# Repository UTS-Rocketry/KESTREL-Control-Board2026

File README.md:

# CAS Interface Board 2026

Control Actuation System (CAS) Interface Board for the UTS Rocketry avionics stack.

This board provides closed-loop control for the airbrake and parafoil control systems, along with sensor interfaces and onboard data logging. The design is based on the STM32F405RGT6 microcontroller and integrates inertial sensing, actuator control, and non-volatile storage.

The CAS board is intended to operate as part of the UTS Rocketry flight avionics architecture.

---

## Overview

The CAS Interface Board is responsible for:

- Airbrake deployment control
- Roll stabilisation control
- Sensor acquisition
- Data logging
- Actuator interfacing

Closed-loop control is performed onboard using IMU, barometric sensor, and GPS measurements.

---

## Hardware

### Microcontroller

STM32F405RGT6

- ARM Cortex-M4F
- 168 MHz
- Hardware floating point
- 1 MB Flash
- 192 KB RAM

---

### Sensors

#### IMU

LSM6DS3TR-C

Interface:

- SPI (4-wire)

Signals:

- SCK
- MOSI
- MISO
- CS
- DRDY Interrupt

Power:

- 3.3 V

---

#### Barometer

Interface:

- I2C

Signals:

- SCL
- SDA

Power:

- 3.3 V

---

### Storage

#### MicroSD Card

Interface:

- SPI

Signals:

- SCK
- MOSI
- MISO
- CS

Purpose:

- Flight data logging

---

### Actuator Interfaces

#### Servo Outputs

- Airbrake Servo
- Roll Control Servo

Control Method:

- Timer PWM outputs

Power:

- Dedicated 5 V servo rail

Signal Voltage:

- 3.3 V logic

---

## Control System

### Airbrake Control

The CAS system predicts apogee using altitude and velocity estimates derived from sensor measurements.

Airbrake deployment is adjusted to reach the target apogee.

Inputs:

- Barometer altitude
- Estimated vertical velocity

Outputs:

- Airbrake servo PWM

## Firmware

Development tools:

- STM32CubeMX
- STM32CubeIDE
- ST-Link

Features:

- SPI IMU driver
- I2C barometer driver
- PWM servo control
- SD card logging
- Flash logging
- Interrupt-driven sensor acquisition

---

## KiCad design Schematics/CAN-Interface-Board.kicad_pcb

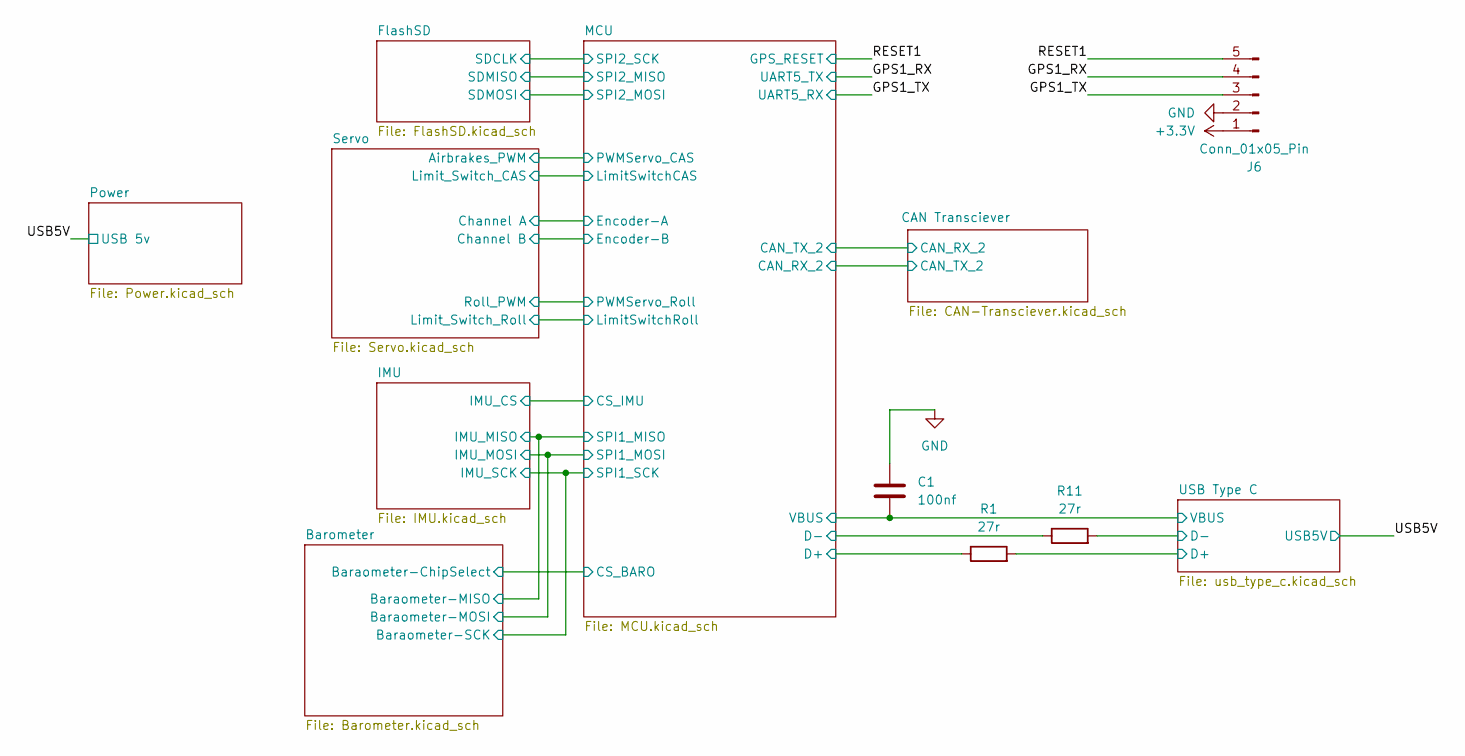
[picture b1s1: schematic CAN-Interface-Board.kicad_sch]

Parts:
C1: 100nf; C_0805_2012Metric_Pad1.18x1.45mm_HandSolder; LCSC C49678
J6: Conn_01x05_Pin; JST_XH_B5B-XH-A_1x05_P2.50mm_Vertical; LCSC C157991
R1, R11: 27r; R_0805_2012Metric_Pad1.20x1.40mm_HandSolder; LCSC C17594

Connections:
+3.3V: J6.1; also elsewhere on the board
/GPS1_RX: J6.4; also elsewhere on the board
/GPS1_TX: J6.3; also elsewhere on the board
/MCU/D+: R1.1; also elsewhere on the board
/MCU/D-: R11.1; also elsewhere on the board
/RESET1: J6.5; also elsewhere on the board
/USB5V: C1.2; also elsewhere on the board
/USB Type C/D+: R1.2; also elsewhere on the board
/USB Type C/D-: R11.2; also elsewhere on the board
GND: C1.1, J6.2; also elsewhere on the board

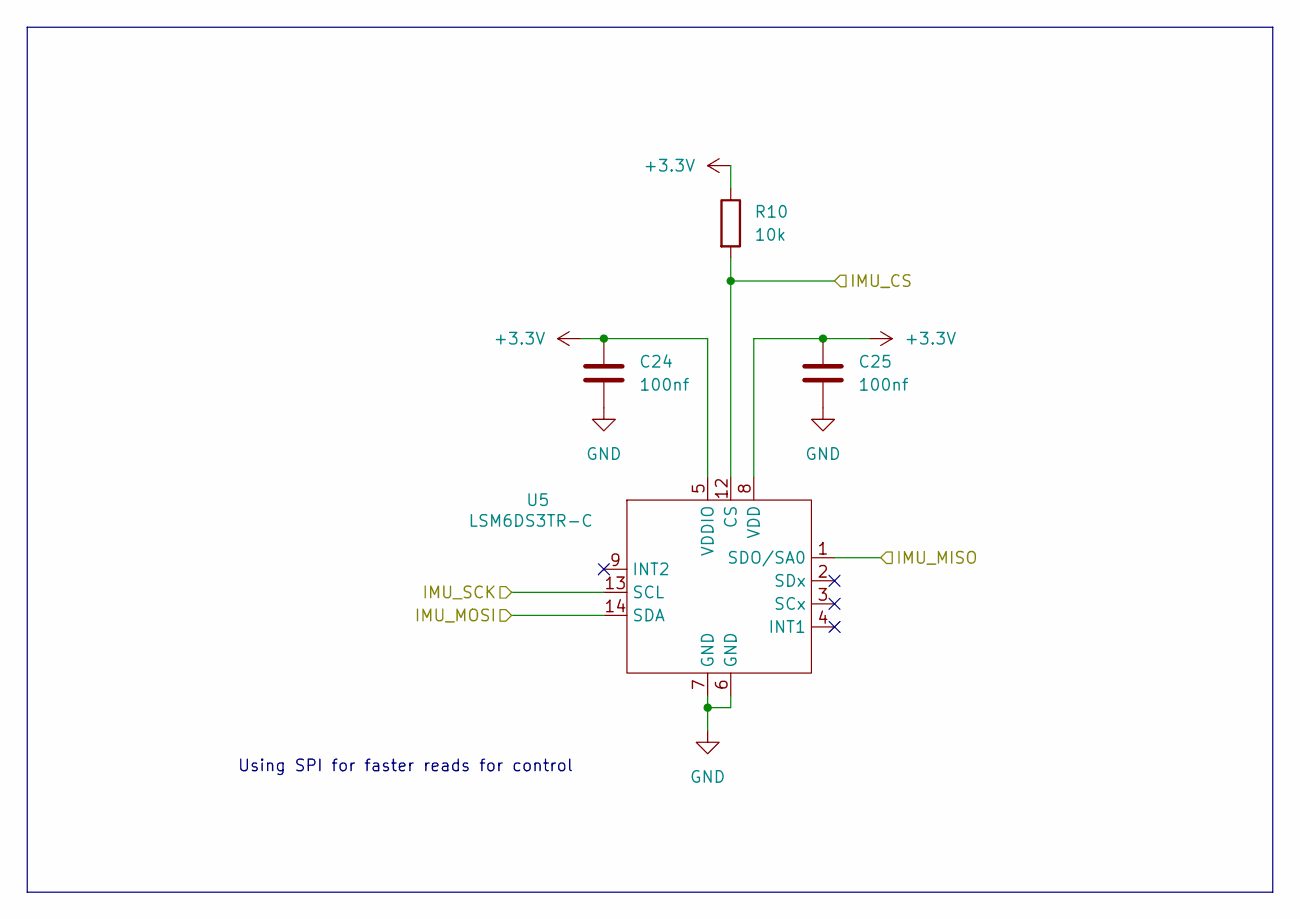
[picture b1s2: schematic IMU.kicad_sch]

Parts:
C24, C25: 100nf; C_0805_2012Metric_Pad1.18x1.45mm_HandSolder; LCSC Part C49678
R10: 10k; R_0805_2012Metric_Pad1.20x1.40mm_HandSolder; LCSC C84376
U5: LSM6DS3TR-C; LGA-14-2.5X3MM; LCSC Part C967633

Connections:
+3.3V: C24.1, C25.1, R10.1, U5.5 (VDDIO), U5.8 (VDD); also elsewhere on the board
/Barometer/Baraometer-MISO: U5.1 (SDO/SA0); also elsewhere on the board
/Barometer/Baraometer-MOSI: U5.14 (SDA); also elsewhere on the board
/Barometer/Baraometer-SCK: U5.13 (SCL); also elsewhere on the board
/IMU/IMU_CS: R10.2, U5.12 (CS); also elsewhere on the board
GND: C24.2, C25.2, U5.6 (GND), U5.7 (GND); also elsewhere on the board

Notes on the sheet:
Using SPI for faster reads for control

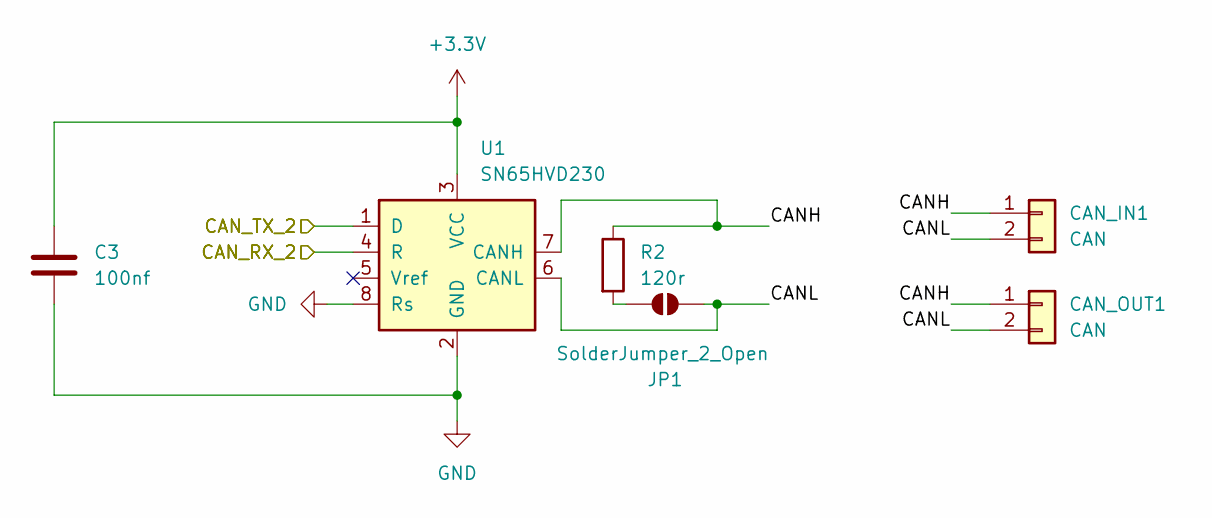
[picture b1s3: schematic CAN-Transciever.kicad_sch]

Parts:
C3: 100nf; C_0805_2012Metric_Pad1.18x1.45mm_HandSolder; LCSC Part C49678
CAN_IN1: CAN; MOLEX_26013114; LCSC Part C17644051
CAN_OUT1: CAN; MOLEX_26013114; LCSC Part C17644051
JP1: SolderJumper_2_Open; SolderJumper-2_P1.3mm_Open_TrianglePad1.0x1.5mm; LCSC C474893
R2: 120r; R_0805_2012Metric_Pad1.20x1.40mm_HandSolder; LCSC Part C269726
U1: SN65HVD230; SOIC-8_3.9x4.9mm_P1.27mm; LCSC Part C1543812

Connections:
+3.3V: C3.1, U1.3 (VCC); also elsewhere on the board
/CAN Transciever/CANH: CAN_IN1.1, CAN_OUT1.1, R2.1, U1.7 (CANH)
/CAN Transciever/CANL: CAN_IN1.2, CAN_OUT1.2, JP1.2 (B), U1.6 (CANL)
/CAN Transciever/CAN_RX_2: U1.4 (R); also elsewhere on the board
/CAN Transciever/CAN_TX_2: U1.1 (D); also elsewhere on the board
GND: C3.2, U1.2 (GND), U1.8 (Rs); also elsewhere on the board
unnamed: JP1.1 (A), R2.2

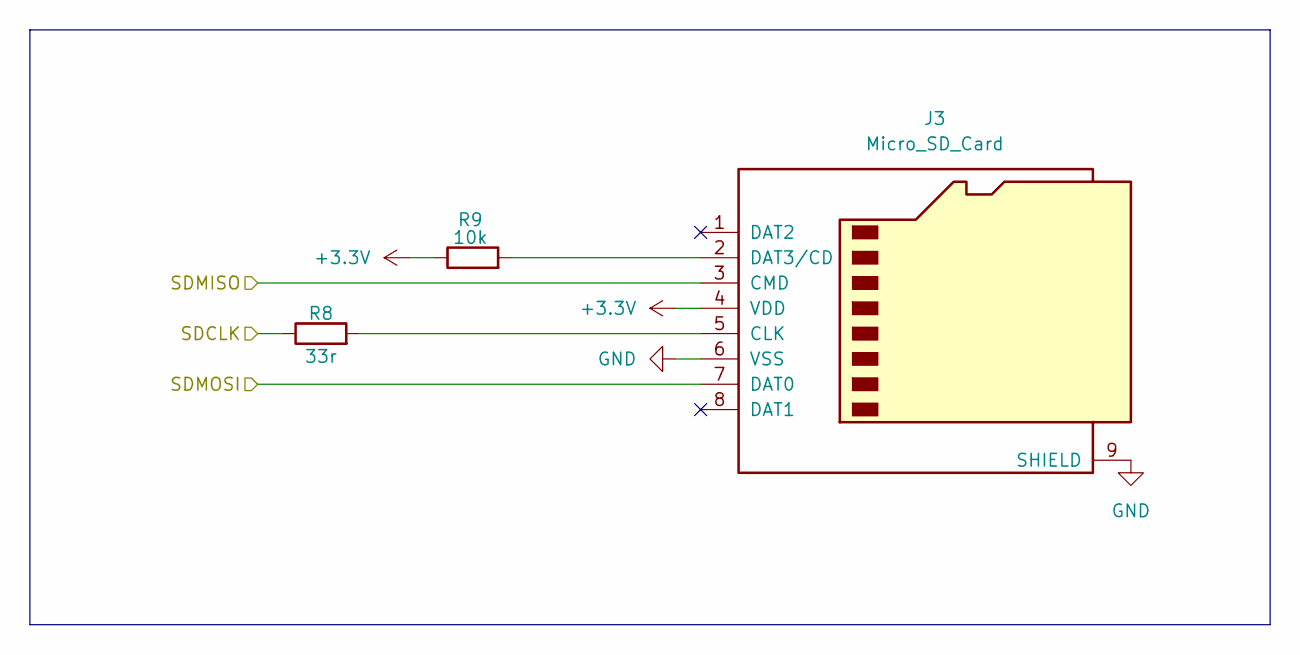
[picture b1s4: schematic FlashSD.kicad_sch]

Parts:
J3: Micro_SD_Card; microSD_HC_Molex_47219-2001; LCSC Part C164170
R8: 33r; R_0805_2012Metric_Pad1.20x1.40mm_HandSolder; LCSC Part C17557
R9: 10k; R_0805_2012Metric_Pad1.20x1.40mm_HandSolder; LCSC Part C84376

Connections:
+3.3V: J3.4 (VDD), R9.1; also elsewhere on the board
/FlashSD/SDCLK: R8.1; also elsewhere on the board
/FlashSD/SDMISO: J3.3 (CMD); also elsewhere on the board
/FlashSD/SDMOSI: J3.7 (DAT0); also elsewhere on the board
GND: J3.6 (VSS), J3.9 (SHIELD); also elsewhere on the board
unnamed: J3.5 (CLK), R8.2
unnamed: J3.2 (DAT3/CD), R9.2

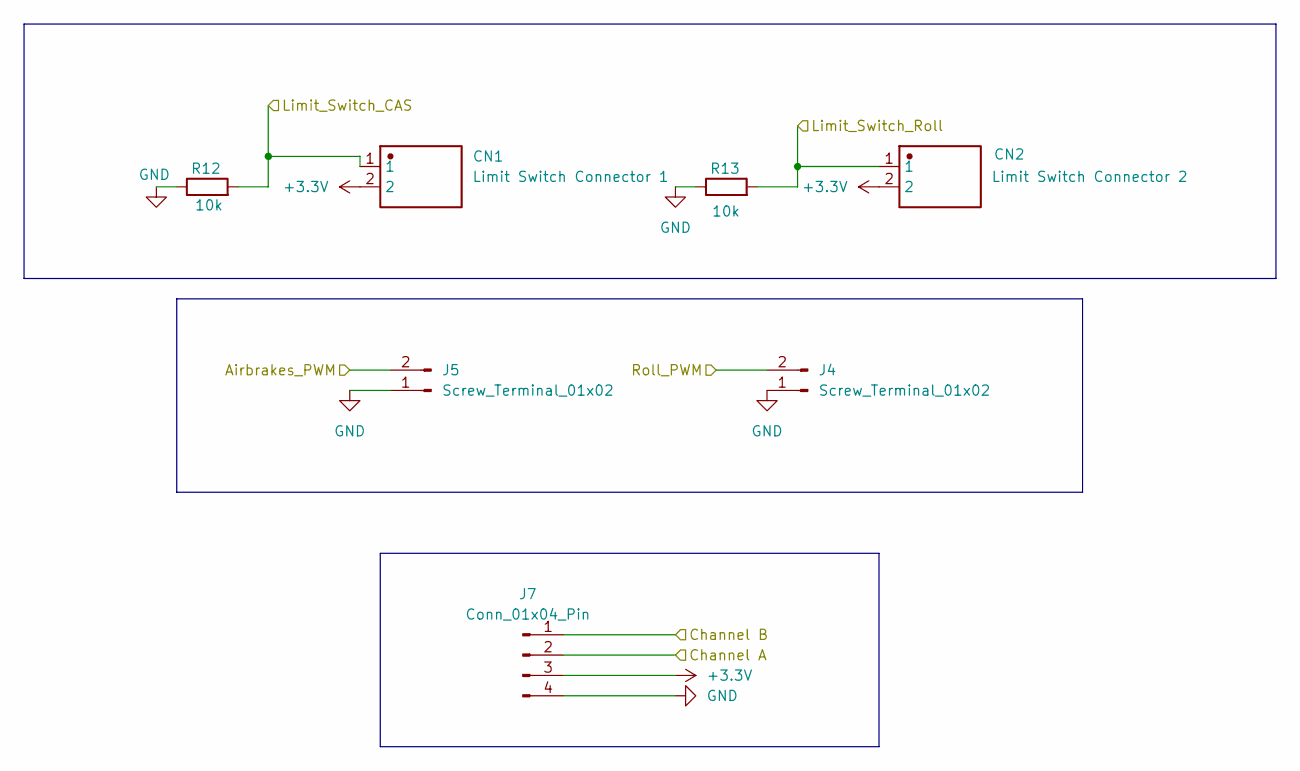
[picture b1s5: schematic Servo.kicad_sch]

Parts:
CN1: Limit Switch Connector 1; JST_EH_B2B-EH-A_1x02_P2.50mm_Vertical; LCSC Part C158012
CN2: Limit Switch Connector 2; JST_EH_B2B-EH-A_1x02_P2.50mm_Vertical; LCSC Part C158012
J4, J5: Screw_Terminal_01x02; JST_EH_B2B-EH-A_1x02_P2.50mm_Vertical; LCSC C158012
J7: Conn_01x04_Pin; JST_PH_B4B-PH-K_1x04_P2.00mm_Vertical; LCSC C131334
R12, R13: 10k; R_0805_2012Metric_Pad1.20x1.40mm_HandSolder; LCSC Part C4277843

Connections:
+3.3V: CN1.2, CN2.2, J7.3; also elsewhere on the board
/MCU/Encoder-A: J7.2; also elsewhere on the board
/MCU/Encoder-B: J7.1; also elsewhere on the board
/MCU/LimitSwitchCAS: CN1.1, R12.2; also elsewhere on the board
/MCU/LimitSwitchRoll: CN2.1, R13.2; also elsewhere on the board
/MCU/PWMServo_CAS: J5.2; also elsewhere on the board
/MCU/PWMServo_Roll: J4.2; also elsewhere on the board
GND: J4.1, J5.1, J7.4, R12.1, R13.1; also elsewhere on the board

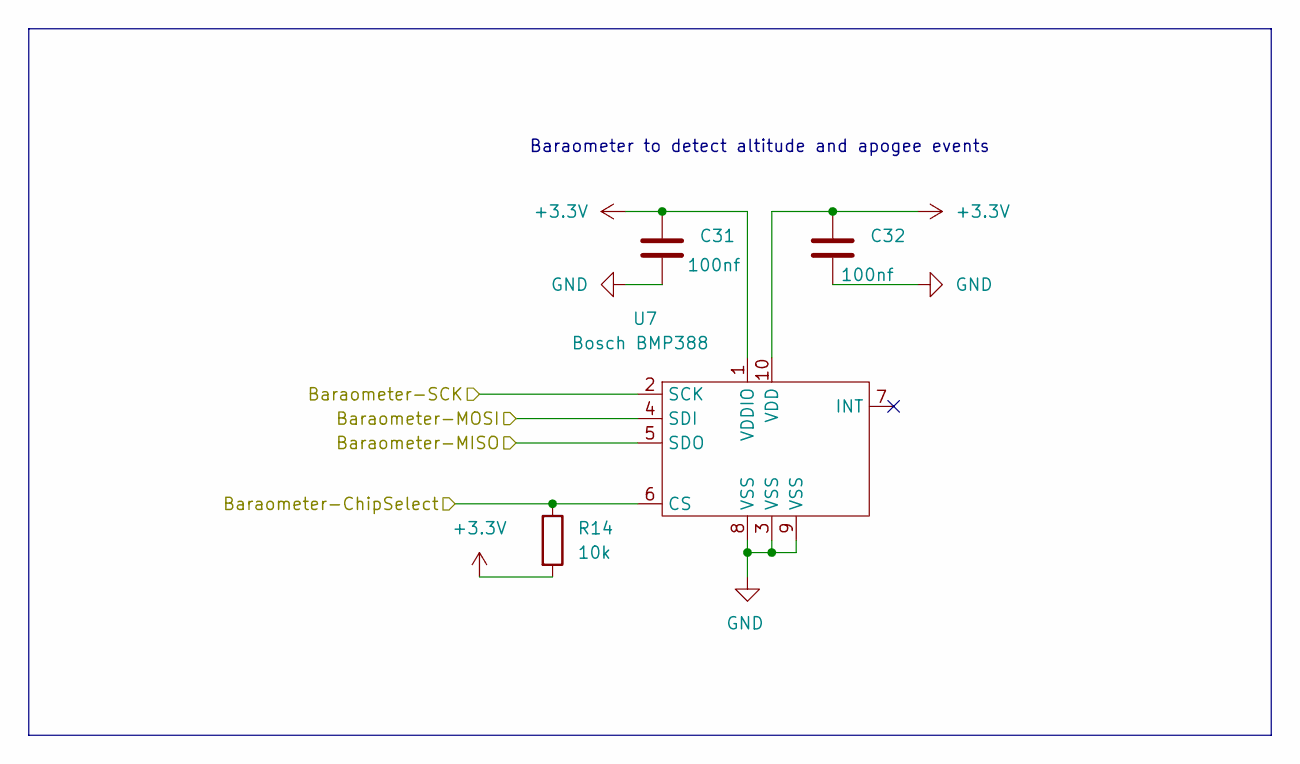
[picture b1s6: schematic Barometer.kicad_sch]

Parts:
C31, C32: 100nf; C_0805_2012Metric_Pad1.18x1.45mm_HandSolder; LCSC C49678
R14: 10k; R_0805_2012Metric_Pad1.20x1.40mm_HandSolder; LCSC C84376
U7: Bosch BMP388; PQFN50P200X200X80-10N; LCSC C779278

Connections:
+3.3V: C31.1, C32.1, R14.2, U7.1 (VDDIO), U7.10 (VDD); also elsewhere on the board
/Barometer/Baraometer-ChipSelect: R14.1, U7.6 (CS); also elsewhere on the board
/Barometer/Baraometer-MISO: U7.5 (SDO); also elsewhere on the board
/Barometer/Baraometer-MOSI: U7.4 (SDI); also elsewhere on the board
/Barometer/Baraometer-SCK: U7.2 (SCK); also elsewhere on the board
GND: C31.2, C32.2, U7.3 (VSS), U7.8 (VSS), U7.9 (VSS); also elsewhere on the board

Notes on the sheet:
Baraometer to detect altitude and apogee events

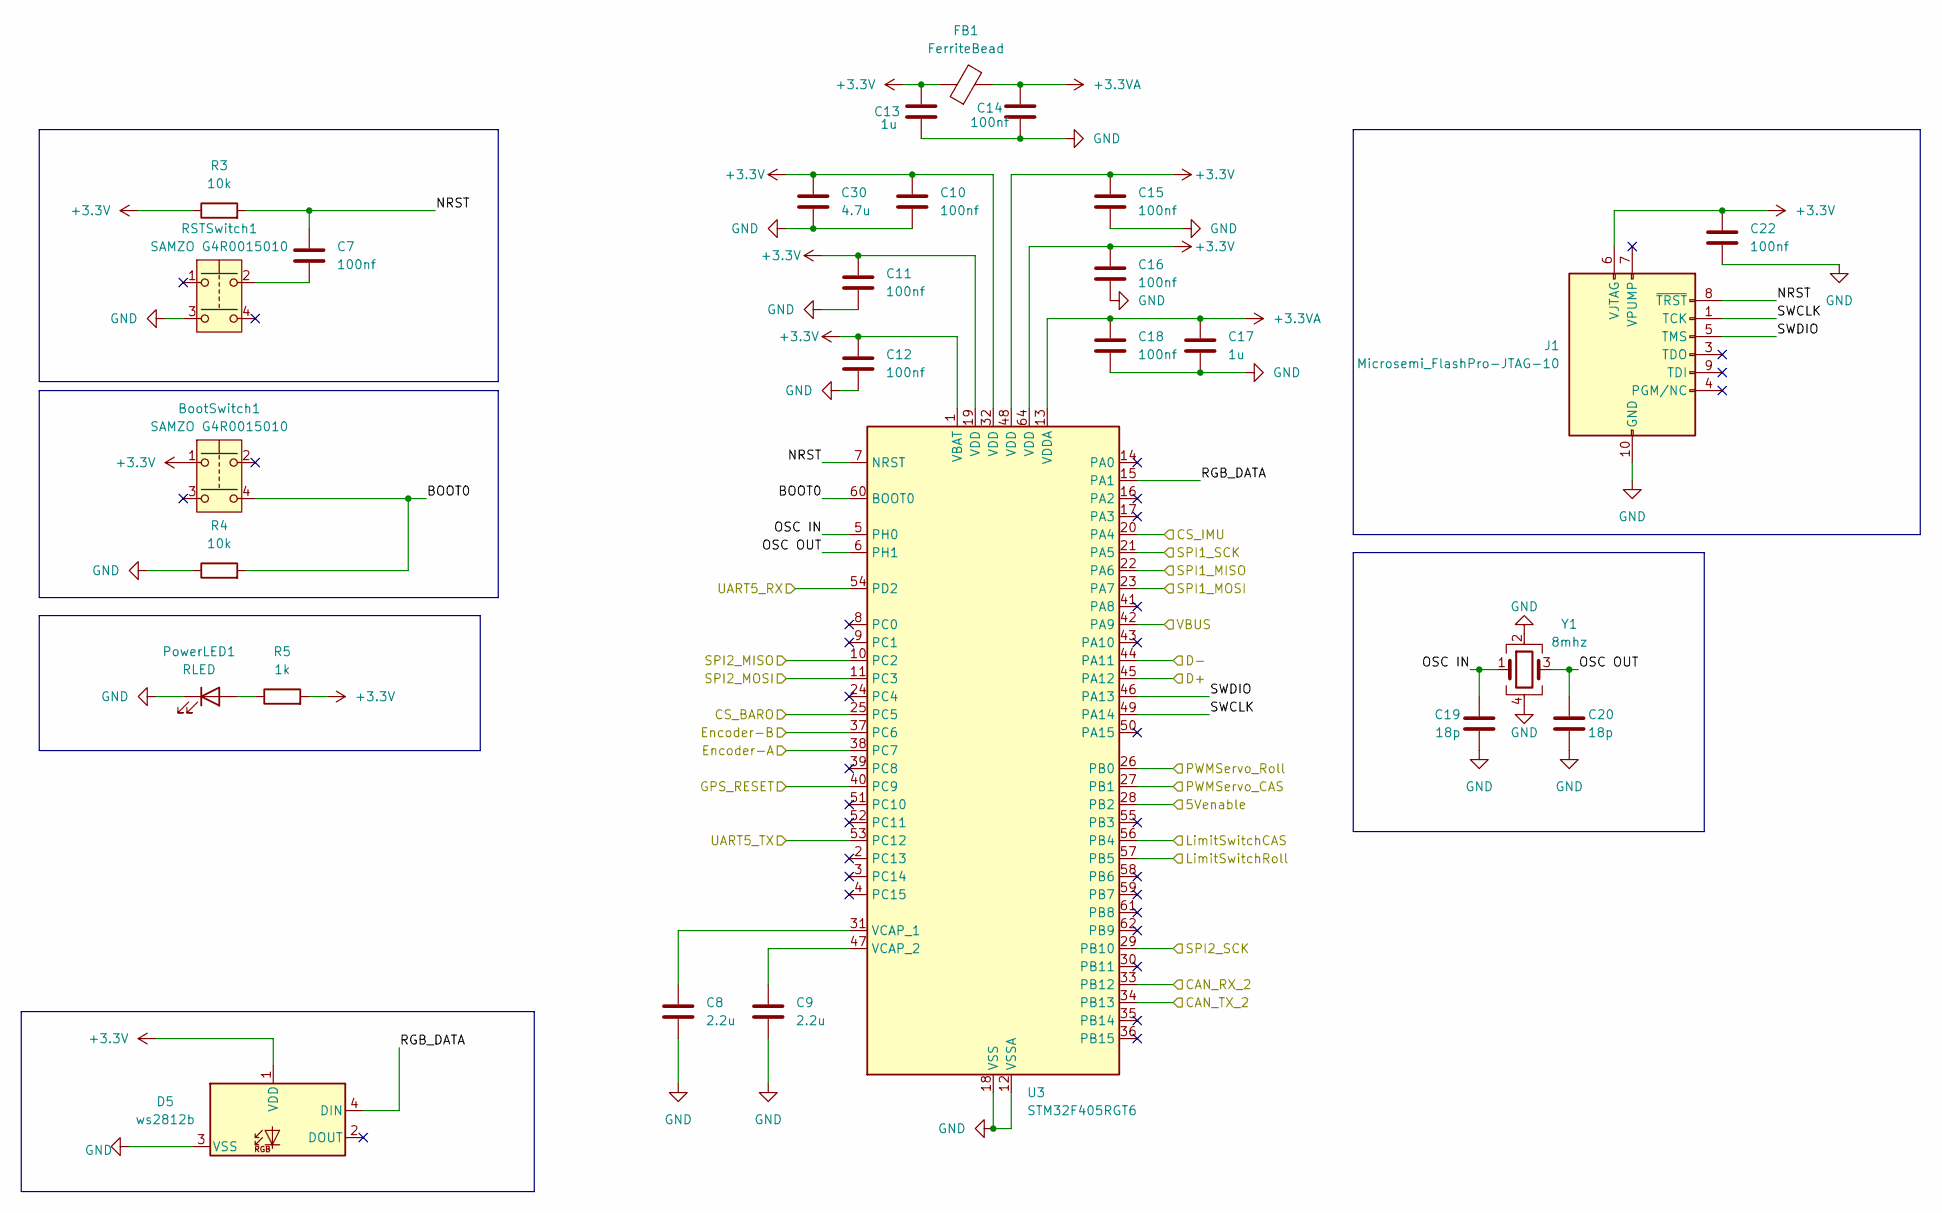
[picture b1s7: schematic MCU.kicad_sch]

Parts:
BootSwitch1: SAMZO G4R0015010; LCSC Part C49393646
C7: 100nf; C_0805_2012Metric_Pad1.18x1.45mm_HandSolder; LCSC Part C49678
C8, C9: 2.2u; C_0805_2012Metric_Pad1.18x1.45mm_HandSolder; LCSC C19110
C10, C11, C12, C14, C15, C16, C18, C22: 100nf; C_0805_2012Metric_Pad1.18x1.45mm_HandSolder; LCSC C49678
C13, C17: 1u; C_0805_2012Metric_Pad1.18x1.45mm_HandSolder; LCSC C28323
C19, C20: 18p; C_0805_2012Metric_Pad1.18x1.45mm_HandSolder; LCSC Part C170109
C30: 4.7u; C_0805_2012Metric_Pad1.18x1.45mm_HandSolder; LCSC C98192
D5: ws2812b; LED_WS2812B_PLCC4_5.0x5.0mm_P3.2mm; LCSC C2761795
FB1: FerriteBead; R_0805_2012Metric_Pad1.20x1.40mm_HandSolder; LCSC C85840
J1: Microsemi_FlashPro-JTAG-10; PinHeader_2x05_P1.27mm_Vertical; LCSC Part C22438120
PowerLED1: RLED; LED_0603_1608Metric_Pad1.05x0.95mm_HandSolder; LCSC Part C965799
R3: 10k; R_0805_2012Metric_Pad1.20x1.40mm_HandSolder; LCSC Part C84376
R4: 10k; R_0805_2012Metric_Pad1.20x1.40mm_HandSolder; LCSC Part C96346
R5: 1k; R_0805_2012Metric_Pad1.20x1.40mm_HandSolder; LCSC Part C95781
RSTSwitch1: SAMZO G4R0015010; LCSC Part C49393646
U3: STM32F405RGT6; LQFP-64_10x10mm_P0.5mm; LCSC C15742
Y1: 8mhz; Crystal_SMD_3225-4Pin_3.2x2.5mm_HandSoldering; LCSC Part C19723344

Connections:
+3.3V: BootSwitch1.1, C10.1, C11.1, C12.1, C13.2, C15.1, C16.1, C22.1, C30.1, D5.1 (VDD), FB1.1, J1.6 (VJTAG), R3.1, R5.2, U3.1 (VBAT), U3.19 (VDD), U3.32 (VDD), U3.48 (VDD), U3.64 (VDD); also elsewhere on the board
+3.3VA: C14.2, C17.1, C18.1, FB1.2, U3.13 (VDDA)
/Barometer/Baraometer-ChipSelect: U3.25 (PC5); also elsewhere on the board
/Barometer/Baraometer-MISO: U3.22 (PA6); also elsewhere on the board
/Barometer/Baraometer-MOSI: U3.23 (PA7); also elsewhere on the board
/Barometer/Baraometer-SCK: U3.21 (PA5); also elsewhere on the board
/CAN Transciever/CAN_RX_2: U3.34 (PB13); also elsewhere on the board
/CAN Transciever/CAN_TX_2: U3.33 (PB12); also elsewhere on the board
/FlashSD/SDCLK: U3.29 (PB10); also elsewhere on the board
/FlashSD/SDMISO: U3.10 (PC2); also elsewhere on the board
/FlashSD/SDMOSI: U3.11 (PC3); also elsewhere on the board
/GPS1_RX: U3.53 (PC12); also elsewhere on the board
/GPS1_TX: U3.54 (PD2); also elsewhere on the board
/IMU/IMU_CS: U3.20 (PA4); also elsewhere on the board
/MCU/5Venable: U3.28 (PB2)
/MCU/BOOT0: BootSwitch1.4, R4.2, U3.60 (BOOT0)
/MCU/D+: U3.45 (PA12); also elsewhere on the board
/MCU/D-: U3.44 (PA11); also elsewhere on the board
/MCU/Encoder-A: U3.38 (PC7); also elsewhere on the board
/MCU/Encoder-B: U3.37 (PC6); also elsewhere on the board
/MCU/LimitSwitchCAS: U3.56 (PB4); also elsewhere on the board
/MCU/LimitSwitchRoll: U3.57 (PB5); also elsewhere on the board
/MCU/NRST: C7.1, J1.8 (~TRST), R3.2, U3.7 (NRST)
/MCU/OSC IN: C19.1, U3.5 (PH0), Y1.1
/MCU/OSC OUT: C20.1, U3.6 (PH1), Y1.3
/MCU/PWMServo_CAS: U3.27 (PB1); also elsewhere on the board
/MCU/PWMServo_Roll: U3.26 (PB0); also elsewhere on the board
/MCU/RGB_DATA: D5.4 (DIN), U3.15 (PA1)
/MCU/SWCLK: J1.1 (TCK), U3.49 (PA14)
/MCU/SWDIO: J1.5 (TMS), U3.46 (PA13)
/RESET1: U3.40 (PC9); also elsewhere on the board
/USB5V: U3.42 (PA9); also elsewhere on the board
GND: C8.2, C9.2, C10.2, C11.2, C12.2, C13.1, C14.1, C15.2, C16.2, C17.2, C18.2, C19.2, C20.2, C22.2, C30.2, D5.3 (VSS), J1.2 (GND), J1.10 (GND), PowerLED1.1 (K), R4.1, RSTSwitch1.3, U3.12 (VSSA), U3.18 (VSS), U3.63 (VSS), Y1.2, Y1.4; also elsewhere on the board
unnamed: C7.2, RSTSwitch1.2
unnamed: PowerLED1.2 (A), R5.1
unnamed: C8.1, U3.31 (VCAP_1)
unnamed: C9.1, U3.47 (VCAP_2)

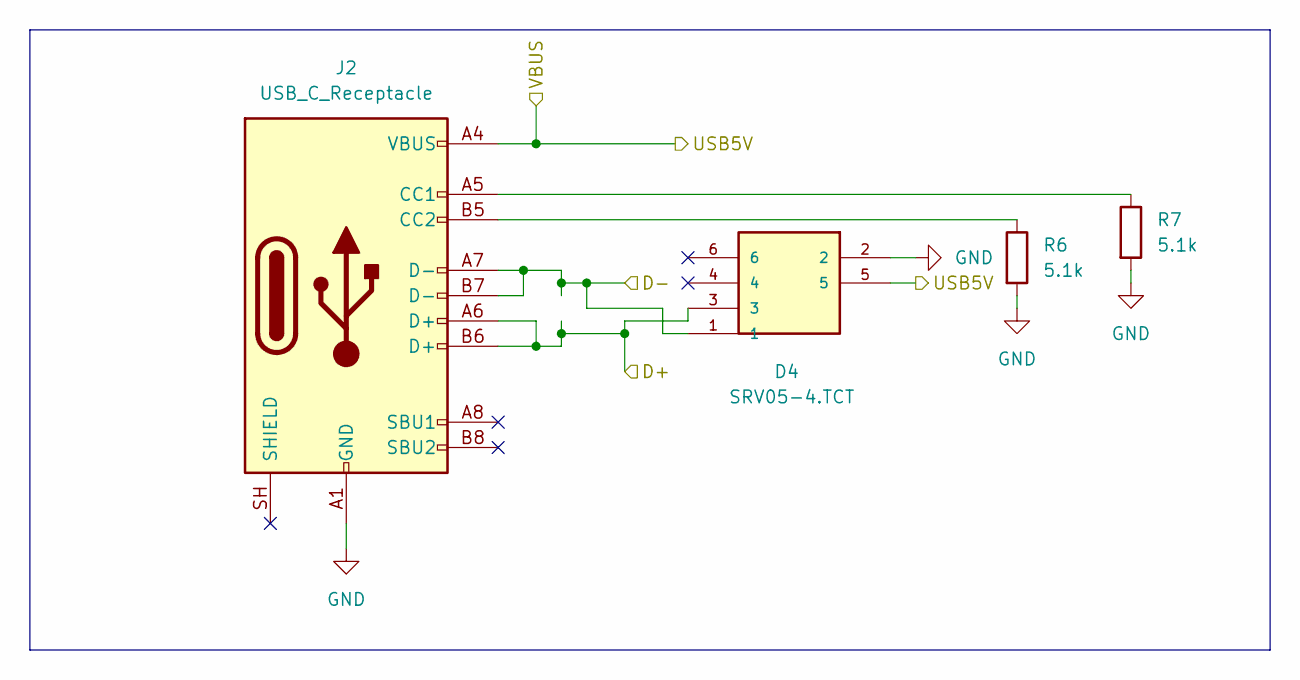
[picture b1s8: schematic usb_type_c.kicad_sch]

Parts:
D4: SRV05-4.TCT; SOT-23-6; MOUSER_PART_NUMBER 947-SRV05-4.TCT
J2: USB_C_Receptacle; USB_C_Receptacle_HRO_TYPE-C-31-M-12; LCSC C165948
R6, R7: 5.1k; R_0805_2012Metric_Pad1.20x1.40mm_HandSolder; LCSC C27834

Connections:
/USB5V: D4.5, J2.A4 (VBUS), J2.A9 (VBUS), J2.B4 (VBUS), J2.B9 (VBUS); also elsewhere on the board
/USB Type C/D+: D4.3, J2.A6 (D+), J2.B6 (D+); also elsewhere on the board
/USB Type C/D-: D4.1, J2.A7 (D-), J2.B7 (D-); also elsewhere on the board
GND: D4.2, J2.A1 (GND), J2.A12 (GND), J2.B1 (GND), J2.B12 (GND), R6.2, R7.2; also elsewhere on the board
unnamed: J2.A5 (CC1), R7.1
unnamed: J2.B5 (CC2), R6.1

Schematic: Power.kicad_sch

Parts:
C4: 1u; C_0805_2012Metric_Pad1.18x1.45mm_HandSolder; LCSC Part C28323
C5: 4.7u; C_0805_2012Metric_Pad1.18x1.45mm_HandSolder; LCSC Part C98192
D1, D2: D_Schottky; D_2114_3652Metric; LCSC C113936
PowerIn1: 2 pin Molex; MOLEX_26013114; LCSC C17644051
U2: LDL1117-3.3; SOT230P700X180-4N; LCSC C435835

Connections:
+3.3V: C5.1, U2.3 (Vout), U2.4 (Vout); also elsewhere on the board
+BATT: D1.2 (A), PowerIn1.1
/USB5V: D2.2 (A); also elsewhere on the board
GND: C4.2, C5.2, PowerIn1.2, U2.2 (GND); also elsewhere on the board
unnamed: C4.1, D1.1 (K), D2.1 (K), U2.1 (Vin)

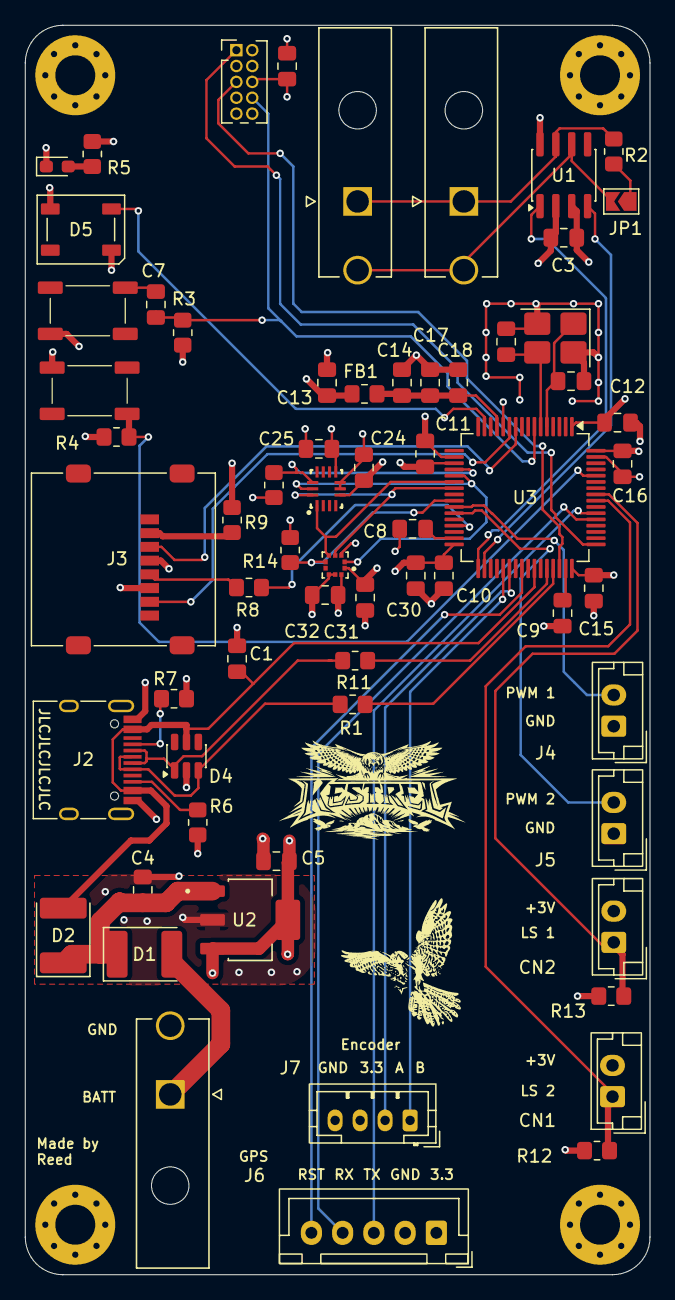
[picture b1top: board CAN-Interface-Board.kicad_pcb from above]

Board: 4 copper layers, 50.0 x 100.0 mm, 65 parts (0 on the bottom side), 47 nets.

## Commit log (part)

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2026-03-16 started new design with esp32
2026-03-17 added esp32 for uart to tune control systems from a web browser app
2026-03-17 finished first layout and routing
2026-03-17 clean up of routing
2026-03-24 updated board waiting on review
2026-03-25 Updating to KiCad 10.0
2026-03-27 removed esp32 to seperate board, added gps breakout, pending final review for purchase
2026-03-27 finished waiting for review
2026-03-30 final draft, in JLPCB cart
2026-03-31 Added encoder connection for parafoil motor position information, in buy order ready for purchase
